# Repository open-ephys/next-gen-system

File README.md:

##  Next generation electrophysiology acquisition core
This repository is a work in progress repository for next generation open
source acquisition and closed-loop feedback system for multichannel
electrophysiology.

This project will hopefully end up being more than just an [open
ephys](http://www.open-ephys.org/) associated standard and will possibly be
moved to a different host org. Ideally we could end up with a set of open, and
evolving interface standards, code blocks and APIs that many different projects
can adapt parts of.

See the [working draft of the
specification](https://open-ephys.atlassian.net/wiki/display/OEW/PCIe+acquisition+board)
for details on the projects goals and desired features.

For now, we are aiming to build a working proof-of-principle prototype that we
can use as starting point to develop proper standards.

## License

### Hardware

<br/>
<span
    xmlns:dct="http://purl.org/dc/terms/" property="dct:title">Open Ephys FMC Intan IO module
</span> 
by 
<a xmlns:cc="http://creativecommons.org/ns#"
href="https://github.com/open-ephys/next-gen-system/" property="cc:attributionName"
rel="cc:attributionURL">Jonathan P. Newman, Jakob Voigts</a> 
is licensed under a
<a rel="license" href="http://creativecommons.org/licenses/by-sa/4.0/">Creative
Commons Attribution-ShareAlike 4.0 International
License</a>.
<br/>
Based on a work at <a xmlns:dct="http://purl.org/dc/terms/"
href="https://github.com/open-ephys/next-gen-system"
rel="dct:source">https://github.com/open-ephys/next-gen-system </a>

### Software
To be decided. Will likely be different licences for different layers of the
system (e.g. the firmware and devices drivers versus APIs and language bindings
versus plugins for various applications).

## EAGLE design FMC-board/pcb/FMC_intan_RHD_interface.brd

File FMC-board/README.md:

# FMC Daughter Board

### Documentation

This board roughly conforms to the VITA 57 standard for LPC (low pin count) FMCs (FPGA Mezzanine Card).

It contains:
- 3x direct SMA connectors to the fpga, with overvoltage diode protection.
- 2x intan compatible 12pin omnetics connectors (A & B) for the intan headstage SPI standard, wired directly to the fpga, with a power supply.
- 1x isolated intan compatible connector (C) isolated through LVDS to CMOS converters and galvanic isolators. This headstage has its own power supply that is fed through am isolated DC-DC converter.
- 3x directional SMA connectors (on the card front edge) that are routed through the same isolation circuit as headstage connector C

The overall proposed architecture of the system is outlined [here](https://open-ephys.atlassian.net/wiki/display/OEW/PCIe+acquisition+board)

### Pinout
FMC LPC pinout can be found [here](https://docs.google.com/spreadsheets/d/18WfmbLGt8bGUUdksKp6AKA_wMX2SJ3Tndin-nnEgUCs/edit#gid=584734392)

### BOM
The bill of materials for this device can be found
[here](https://docs.google.com/spreadsheets/d/18WfmbLGt8bGUUdksKp6AKA_wMX2SJ3Tndin-nnEgUCs/edit?usp=sharing).

## Manufacturing requirements
- 4 layers
- 8mil trace width & spacing
- 12mil min. drill

There is one 0.05" pitch BGA connector (the samtech FMC connector) and a few omnetics connectors with inacessible pins on the board, so a stencil and reflow soldering need to be used.

The samtech FMC connector might need to be clamped or held down during reflow soldering. The samtec docs state that they should settle on their own during reflow though, so trying that first seems like a good idea (  http://suddendocs.samtec.com/processing/searay_soldering1.pdf ).

There is a round pad of kapton tape on the connector to provide a clamping surface for this purpose. We have had good success with using a steel paperclip that we modified to exert less force by cutting two slots into the spring. The original paper clips push down too hard and can warp the conenctor. Possibly just weighting it down with a suitable object could also work. Finally, the size of the connector means that it heats up pretty slowly, so expect it to reflow after everything else on the board, and if possible use proper pre-heating.

In order to meet approximately correct trace impedances, the design further is assuming:
 - 1oz copper
 - ~1.2mm total board height, ~0.25mm per layer, dielectric ER = 4.5

## TODO (Rev 1.0)
- [ ] Instead of conforming to VITA 57, PCB footprint should be made to fit in
  a PC expansion slot and be connected to the KC705 using a flex [FMC
  cable](http://suddendocs.samtec.com/prints/hdr-169472-xx-mkt.pdf). This will
  modularize the IO modules, potentially creating an ecosystem of different
  modules for different applications. It will also use extremely standardized
  interface (rear PC expansion slots) which also have excellent
  electrical/mechanical characteristics.
    - A couple interesting IO Module ideas
        - Analog module (e.g. NI DAQ replacement with some beefy multiplex SAR
          ADC and DAC on it)
        - Isolated Intan module (Similar to existing design, featuring galvanic
          isolation)
        - Adjustable logic level digital IO module
        - SPI compression module
        - Etc...
- [ ] As per [page 24 of the KC705 user
  guide](http://www.xilinx.com/support/documentation/boards_and_kits/kc705/ug810_KC705_Eval_Bd.pdf)
  we need to jumper the TDI and TDO pins of our FMC connectors to allow pass
  through of JTAG signals so the FPGA can be programmed when the FMC module is
  connected.
- [ ] For galvanically isolated IO module, we should conform to human use
  standards. Jakob has some info on what is required for this.

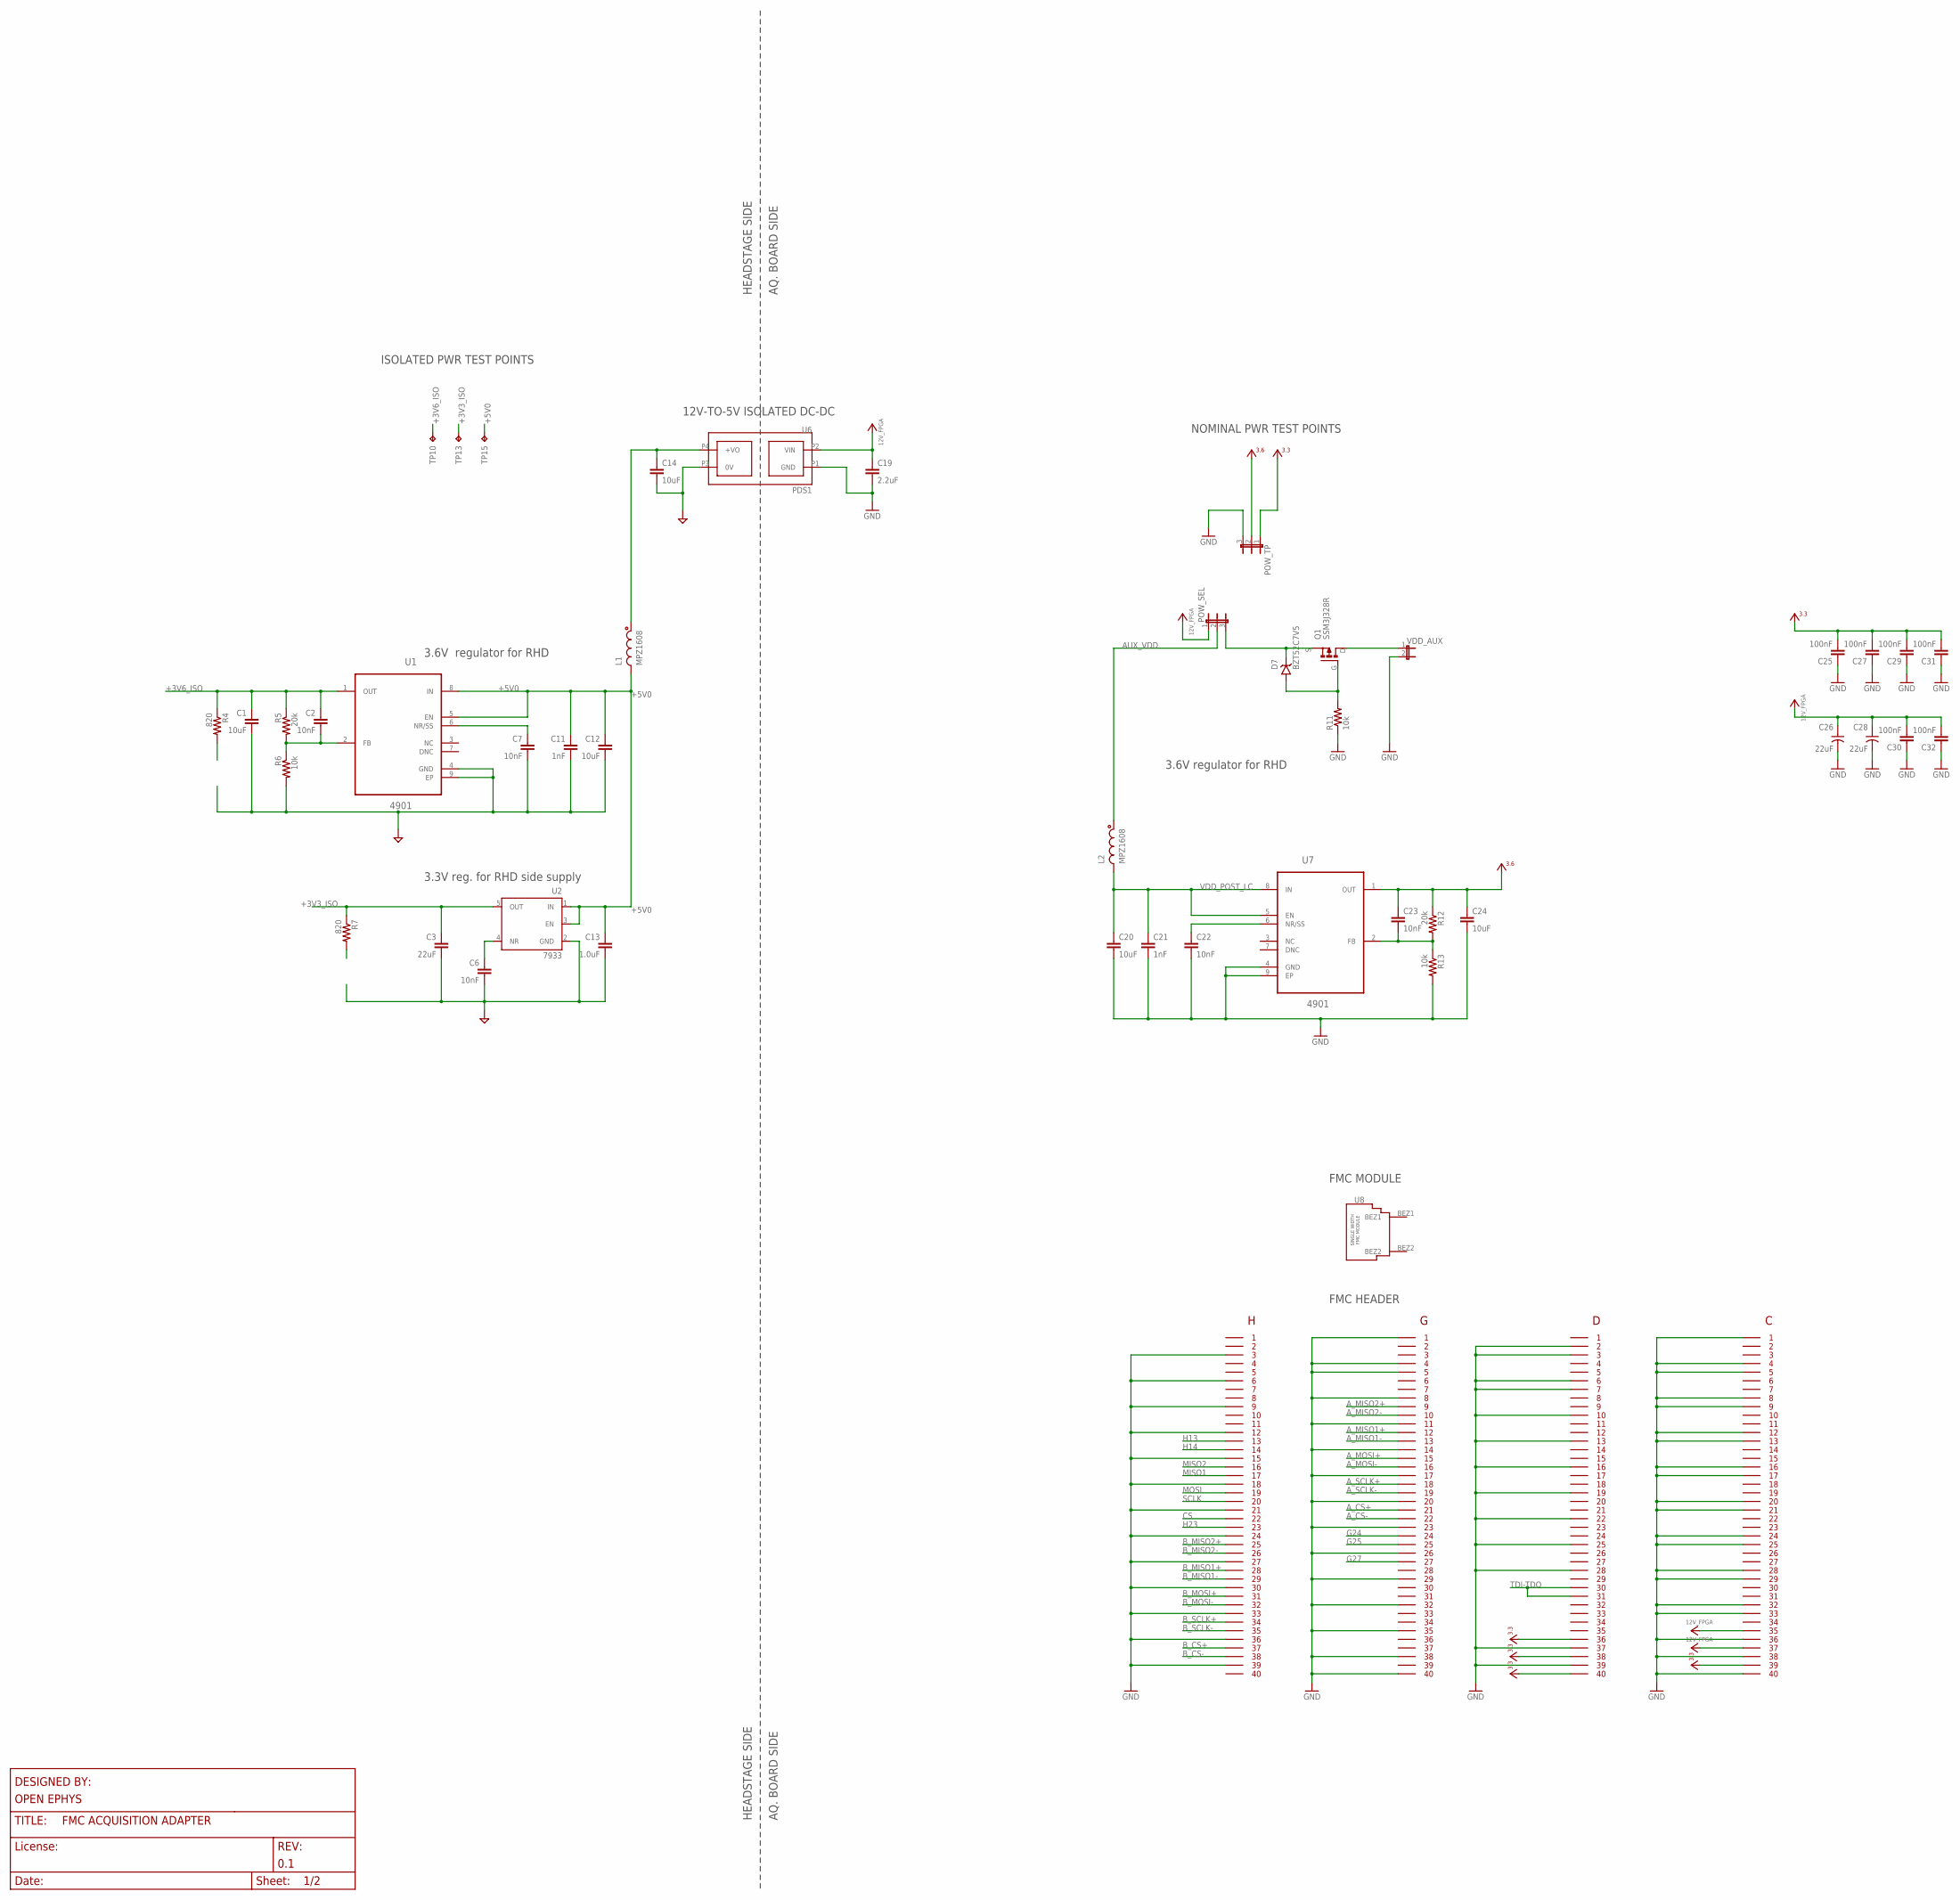
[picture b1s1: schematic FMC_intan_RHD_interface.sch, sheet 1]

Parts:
C1, C12, C14, C20, C24: 10uF; 1206
C2, C6, C7, C22, C23: 10nF; 0603
C3: 22uF; 1206
C11, C21: 1nF; 0603
C13: 1.0uF; 0805
C19: 2.2uF; 1206
C25, C27, C29, C30, C31, C32: 100nF; 0603
C26, C28: 22uF; 1210-POL
D7: BZT52C7V5; SOD123
FMC: FMC_LPC_160_PIN; FMC_LPC_MALE_WITH_SP601_BSILK
L1, L2: MPZ1608; 0603
POW_SEL: JP3E; JP3
POW_TP: JP3E; JP3
Q1: SSM3J328R; SOT23-GSD
R4, R7: 820; 0603
R5, R12: 20k; 0603
R6, R11, R13: 10k; 0603
TP10: +3V6; TP06R
TP13: +3V3; TP06R
TP15: +5V0; TP06R
U1, U7: 4901; SOP65P490X110-9N
U2: 7933; SOT-23-5
U6: PDS1
U8: FMC_SINGLE_WIDTH_MODULE
VDD_AUX: JP2E_THRU-HOLE; JP2

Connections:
12V_FPGA: C19.1, C26.+, C28.+, C30.2, C32.2, FMC.P$155, FMC.P$157, POW_SEL.1, U6.P2 (VIN)
+3V3: C25.2, C27.2, C29.2, C31.2, FMC.P$116, FMC.P$118, FMC.P$120, FMC.P$159, POW_TP.1; also elsewhere on the board
+3V3_ISO: C3.1, R7.1, TP13.TP, U2.5 (OUT); also elsewhere on the board
+3V6: C23.1, C24.1, POW_TP.2, R12.1, U7.1 (OUT)
+3V6_ISO: C1.1, C2.1, R4.1, R5.1, TP10.TP, U1.1 (OUT); also elsewhere on the board
+5V0: C11.1, C12.1, C13.1, L1.2, TP15.TP, U1.5 (EN), U1.8 (IN), U2.1 (IN), U2.3 (EN)
+5V0_ISO-PRE: C14.1, L1.1, U6.P4 (+VO)
AGND1: C23.2, R12.2, R13.1, U7.2 (FB)
AGND2: C2.2, R5.2, R6.1, U1.2 (FB)
AUX_VDD: L2.1, POW_SEL.2
A_CS+: FMC.P$61
A_CS-: FMC.P$62
A_MISO1+: FMC.P$52
A_MISO1-: FMC.P$53
A_MISO2+: FMC.P$49
A_MISO2-: FMC.P$50
A_MOSI+: FMC.P$55
A_MOSI-: FMC.P$56
A_SCLK+: FMC.P$58
A_SCLK-: FMC.P$59
B_CS+: FMC.P$37
B_CS-: FMC.P$38
B_MISO1+: FMC.P$28
B_MISO1-: FMC.P$29
B_MISO2+: FMC.P$25
B_MISO2-: FMC.P$26
B_MOSI+: FMC.P$31
B_MOSI-: FMC.P$32
B_SCLK+: FMC.P$34
B_SCLK-: FMC.P$35
CS: FMC.P$22; also elsewhere on the board
G24: FMC.P$64
G25: FMC.P$65
G27: FMC.P$67
GND: C19.2, C20.2, C21.2, C22.2, C24.2, C25.1, C26.-, C27.1, C28.-, C29.1, C30.1, C31.1, C32.1, FMC.GNDA (GND), FMC.GNDB (GND), FMC.P$3, FMC.P$6, FMC.P$9, FMC.P$12, FMC.P$15, FMC.P$18, FMC.P$21, FMC.P$24, FMC.P$27, FMC.P$30, FMC.P$33, FMC.P$36, FMC.P$39, FMC.P$41, FMC.P$44, FMC.P$45, FMC.P$48, FMC.P$51, FMC.P$54, FMC.P$57, FMC.P$60, FMC.P$63, FMC.P$66, FMC.P$69, FMC.P$72, FMC.P$75, FMC.P$78, FMC.P$80, FMC.P$82, FMC.P$83, FMC.P$86, FMC.P$87, FMC.P$90, FMC.P$93, FMC.P$96, FMC.P$99, FMC.P$102, FMC.P$105, FMC.P$108, FMC.P$117, FMC.P$119, FMC.P$121, FMC.P$124, FMC.P$125, FMC.P$128, FMC.P$129, FMC.P$132, FMC.P$133, FMC.P$136, FMC.P$137, FMC.P$140, FMC.P$141, FMC.P$144, FMC.P$145, FMC.P$148, FMC.P$149, FMC.P$152, FMC.P$153, FMC.P$156, FMC.P$158, FMC.P$160, POW_TP.3, R11.1, R13.2, U6.P1 (GND), U7.4 (GND), U7.9 (EP), VDD_AUX.2; also elsewhere on the board
GND_ISO: C1.2, C3.2, C6.2, C7.2, C11.2, C12.2, C13.2, C14.2, R6.2, U1.4 (GND), U1.9 (EP), U2.2 (GND), U6.P3 (0V); also elsewhere on the board
H13: FMC.P$13; also elsewhere on the board
H14: FMC.P$14; also elsewhere on the board
H23: FMC.P$23; also elsewhere on the board
MISO1: FMC.P$17; also elsewhere on the board
MISO2: FMC.P$16; also elsewhere on the board
MOSI: FMC.P$19; also elsewhere on the board
unnamed: C22.1, U7.6 (NR/SS)
unnamed: D7.C, POW_SEL.3, Q1.S
unnamed: C7.1, U1.6 (NR/SS)
unnamed: D7.A, Q1.G, R11.2
unnamed: Q1.D, VDD_AUX.1
unnamed: C6.1, U2.4 (NR)
SCLK: FMC.P$20; also elsewhere on the board
TDI-TDO: FMC.P$110, FMC.P$111
VDD_POST_LC: C20.1, C21.1, L2.2, U7.5 (EN), U7.8 (IN)

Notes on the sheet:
HEADSTAGE SIDE
AQ. BOARD SIDE
3.3V reg. for RHD side supply
3.6V regulator for RHD
12V-TO-5V ISOLATED DC-DC
ISOLATED PWR TEST POINTS
NOMINAL PWR TEST POINTS
3.6V regulator for RHD
FMC HEADER
FMC MODULE

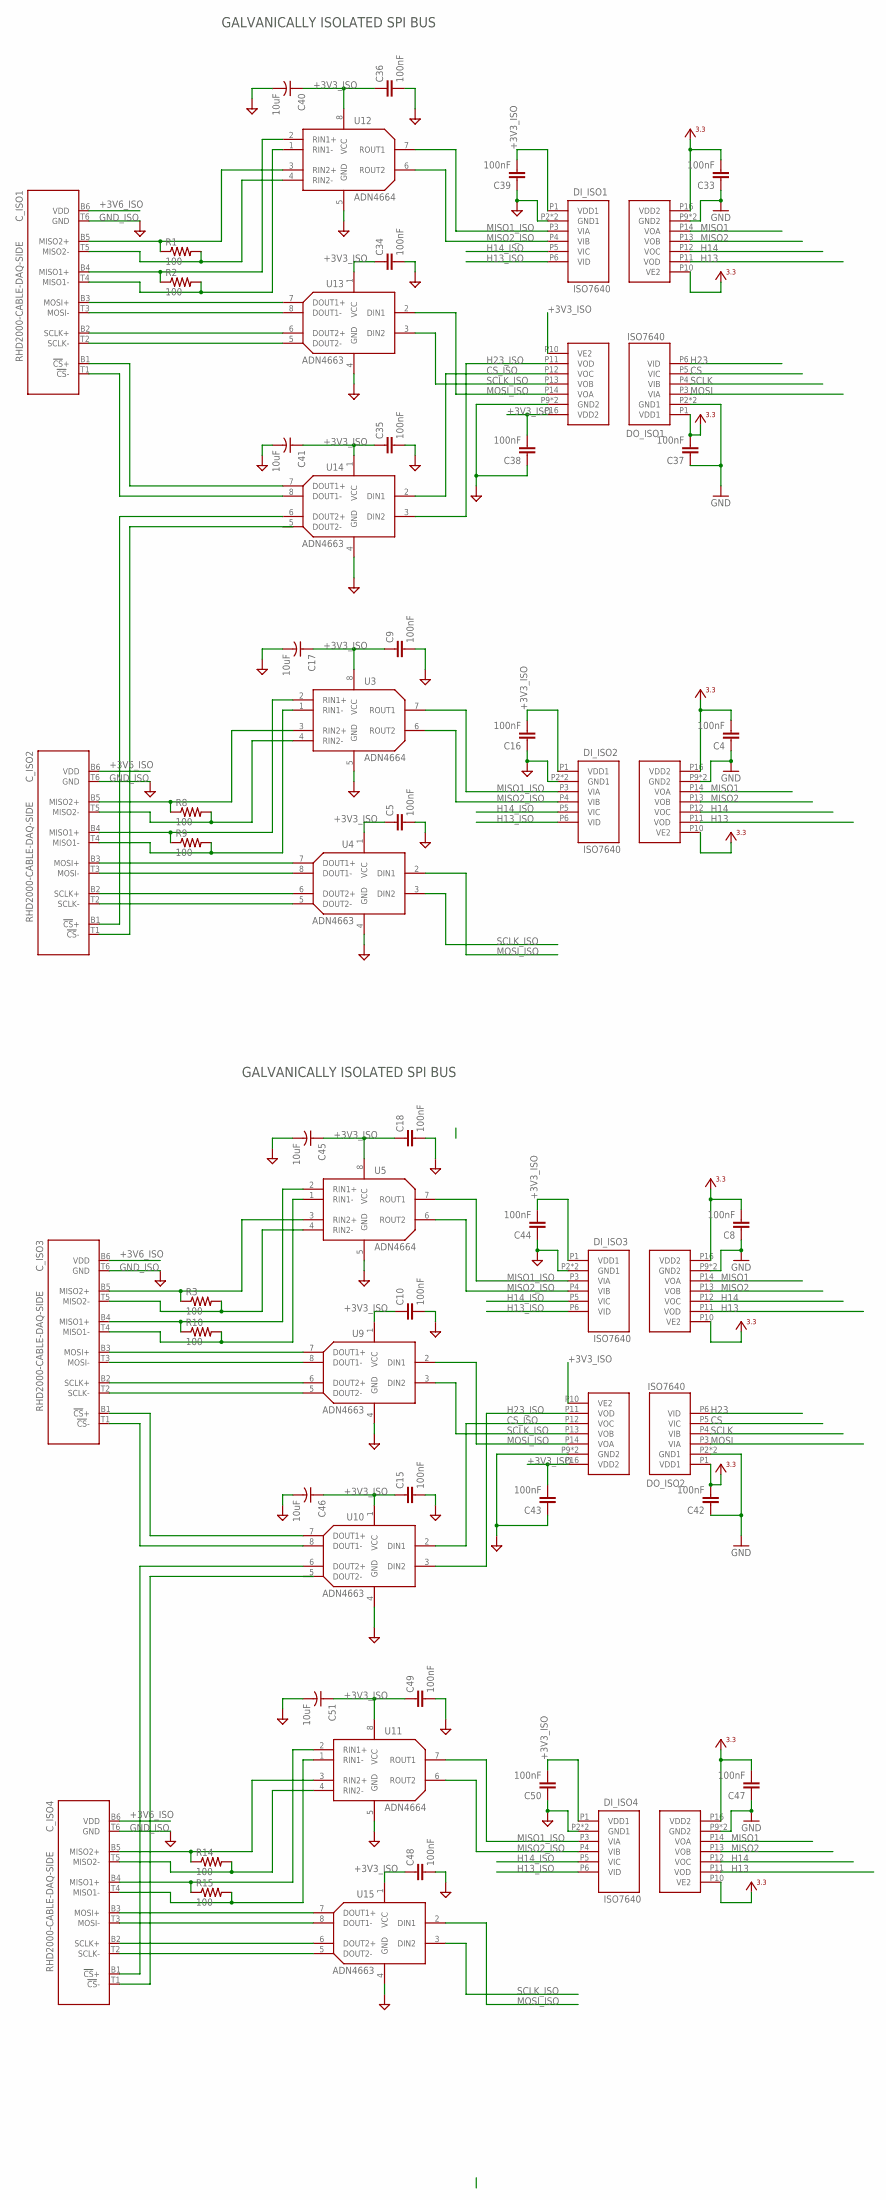
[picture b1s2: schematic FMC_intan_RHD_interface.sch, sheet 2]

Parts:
C4, C5, C8, C9, C10, C15, C16, C18, C33, C34, C35, C36, C37, C38, C39, C42, C43, C44, C47, C48, C49, C50: 100nF; 0603
C17, C40, C41, C45, C46, C51: 10uF; 1206-POL
C_ISO1, C_ISO2, C_ISO3, C_ISO4: RHD2000-CABLE-DAQ-SIDE; OMNETICS_PZN-12-AA
DI_ISO1, DI_ISO2, DI_ISO3, DI_ISO4: ISO7640; SOIC_WIDE_16
DO_ISO1, DO_ISO2: ISO7640; SOIC_WIDE_16
R1, R2, R3, R8, R9, R10, R14, R15: 100; 0603
U3, U5, U11, U12: ADN4664; SOIC127P500X400-8N
U4, U9, U10, U13, U14, U15: ADN4663; SOIC127P500X400-8N

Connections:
+3V3: C4.2, C8.2, C33.2, C37.2, C42.2, C47.2, DI_ISO1.P10 (VE2), DI_ISO1.P16 (VDD2), DI_ISO2.P10 (VE2), DI_ISO2.P16 (VDD2), DI_ISO3.P10 (VE2), DI_ISO3.P16 (VDD2), DI_ISO4.P10 (VE2), DI_ISO4.P16 (VDD2), DO_ISO1.P1 (VDD1), DO_ISO2.P1 (VDD1); also elsewhere on the board
+3V3_ISO: C5.1, C9.1, C10.1, C15.1, C16.2, C17.+, C18.1, C34.1, C35.1, C36.1, C38.2, C39.2, C40.+, C41.+, C43.2, C44.2, C45.+, C46.+, C48.1, C49.1, C50.2, C51.+, DI_ISO1.P1 (VDD1), DI_ISO2.P1 (VDD1), DI_ISO3.P1 (VDD1), DI_ISO4.P1 (VDD1), DO_ISO1.P10 (VE2), DO_ISO1.P16 (VDD2), DO_ISO2.P10 (VE2), DO_ISO2.P16 (VDD2), U3.8 (VCC), U4.1 (VCC), U5.8 (VCC), U9.1 (VCC), U10.1 (VCC), U11.8 (VCC), U12.8 (VCC), U13.1 (VCC), U14.1 (VCC), U15.1 (VCC); also elsewhere on the board
+3V6_ISO: C_ISO1.B6 (VDD), C_ISO2.B6 (VDD), C_ISO3.B6 (VDD), C_ISO4.B6 (VDD); also elsewhere on the board
CS: DO_ISO1.P5 (VIC), DO_ISO2.P5 (VIC); also elsewhere on the board
CS+_ISOLATED1: C_ISO1.B1 (!CS!+), U14.7 (DOUT1+)
CS+_ISOLATED2: C_ISO2.B1 (!CS!+)
CS+_ISOLATED3: C_ISO3.B1 (!CS!+), U10.7 (DOUT1+)
CS+_ISOLATED4: C_ISO4.B1 (!CS!+)
CS-_ISOLATED1: C_ISO1.T1 (!CS!-), U14.8 (DOUT1-)
CS-_ISOLATED2: C_ISO2.T1 (!CS!-)
CS-_ISOLATED3: C_ISO3.T1 (!CS!-), U10.8 (DOUT1-)
CS-_ISOLATED4: C_ISO4.T1 (!CS!-)
CS_ISO: DO_ISO1.P12 (VOC), DO_ISO2.P12 (VOC), U10.2 (DIN1), U14.2 (DIN1)
GND: C4.1, C8.1, C33.1, C37.1, C42.1, C47.1, DI_ISO1.P9 (GND2), DI_ISO1.P15 (GND2), DI_ISO2.P9 (GND2), DI_ISO2.P15 (GND2), DI_ISO3.P9 (GND2), DI_ISO3.P15 (GND2), DI_ISO4.P9 (GND2), DI_ISO4.P15 (GND2), DO_ISO1.P2 (GND1), DO_ISO1.P8 (GND1), DO_ISO2.P2 (GND1), DO_ISO2.P8 (GND1); also elsewhere on the board
GND_ISO: C5.2, C9.2, C10.2, C15.2, C16.1, C17.-, C18.2, C34.2, C35.2, C36.2, C38.1, C39.1, C40.-, C41.-, C43.1, C44.1, C45.-, C46.-, C48.2, C49.2, C50.1, C51.-, C_ISO1.T6 (GND), C_ISO2.T6 (GND), C_ISO3.T6 (GND), C_ISO4.T6 (GND), DI_ISO1.P2 (GND1), DI_ISO1.P8 (GND1), DI_ISO2.P2 (GND1), DI_ISO2.P8 (GND1), DI_ISO3.P2 (GND1), DI_ISO3.P8 (GND1), DI_ISO4.P2 (GND1), DI_ISO4.P8 (GND1), DO_ISO1.P9 (GND2), DO_ISO1.P15 (GND2), DO_ISO2.P9 (GND2), DO_ISO2.P15 (GND2), U3.5 (GND), U4.4 (GND), U5.5 (GND), U9.4 (GND), U10.4 (GND), U11.5 (GND), U12.5 (GND), U13.4 (GND), U14.4 (GND), U15.4 (GND); also elsewhere on the board
H13: DI_ISO1.P11 (VOD), DI_ISO2.P11 (VOD), DI_ISO3.P11 (VOD), DI_ISO4.P11 (VOD); also elsewhere on the board
H13_ISO: DI_ISO1.P6 (VID), DI_ISO2.P6 (VID), DI_ISO3.P6 (VID), DI_ISO4.P6 (VID)
H14: DI_ISO1.P12 (VOC), DI_ISO2.P12 (VOC), DI_ISO3.P12 (VOC), DI_ISO4.P12 (VOC); also elsewhere on the board
H14_ISO: DI_ISO1.P5 (VIC), DI_ISO2.P5 (VIC), DI_ISO3.P5 (VIC), DI_ISO4.P5 (VIC)
H23: DO_ISO1.P6 (VID), DO_ISO2.P6 (VID); also elsewhere on the board
H23_ISO: DO_ISO1.P11 (VOD), DO_ISO2.P11 (VOD), U10.3 (DIN2), U14.3 (DIN2)
MISO1: DI_ISO1.P14 (VOA), DI_ISO2.P14 (VOA), DI_ISO3.P14 (VOA), DI_ISO4.P14 (VOA); also elsewhere on the board
MISO1+_ISOLATED1: C_ISO1.B4 (MISO1+), R2.1, U12.2 (RIN1+)
MISO1+_ISOLATED2: C_ISO2.B4 (MISO1+), R9.1, U3.2 (RIN1+)
MISO1+_ISOLATED3: C_ISO3.B4 (MISO1+), R10.1, U5.2 (RIN1+)
MISO1+_ISOLATED4: C_ISO4.B4 (MISO1+), R15.1, U11.2 (RIN1+)
MISO1-_ISOLATED1: C_ISO1.T4 (MISO1-), R2.2, U12.1 (RIN1-)
MISO1-_ISOLATED2: C_ISO2.T4 (MISO1-), R9.2, U3.1 (RIN1-)
MISO1-_ISOLATED3: C_ISO3.T4 (MISO1-), R10.2, U5.1 (RIN1-)
MISO1-_ISOLATED4: C_ISO4.T4 (MISO1-), R15.2, U11.1 (RIN1-)
MISO1_ISO: DI_ISO1.P3 (VIA), DI_ISO2.P3 (VIA), DI_ISO3.P3 (VIA), DI_ISO4.P3 (VIA), U3.7 (ROUT1), U5.7 (ROUT1), U11.7 (ROUT1), U12.7 (ROUT1)
MISO2: DI_ISO1.P13 (VOB), DI_ISO2.P13 (VOB), DI_ISO3.P13 (VOB), DI_ISO4.P13 (VOB); also elsewhere on the board
MISO2+_ISOLATED1: C_ISO1.B5 (MISO2+), R1.1, U12.3 (RIN2+)
MISO2+_ISOLATED2: C_ISO2.B5 (MISO2+), R8.1, U3.3 (RIN2+)
MISO2+_ISOLATED3: C_ISO3.B5 (MISO2+), R3.1, U5.3 (RIN2+)
MISO2+_ISOLATED4: C_ISO4.B5 (MISO2+), R14.1, U11.3 (RIN2+)
MISO2-_ISOLATED1: C_ISO1.T5 (MISO2-), R1.2, U12.4 (RIN2-)
MISO2-_ISOLATED2: C_ISO2.T5 (MISO2-), R8.2, U3.4 (RIN2-)
MISO2-_ISOLATED3: C_ISO3.T5 (MISO2-), R3.2, U5.4 (RIN2-)
MISO2-_ISOLATED4: C_ISO4.T5 (MISO2-), R14.2, U11.4 (RIN2-)
MISO2_ISO: DI_ISO1.P4 (VIB), DI_ISO2.P4 (VIB), DI_ISO3.P4 (VIB), DI_ISO4.P4 (VIB), U3.6 (ROUT2), U5.6 (ROUT2), U11.6 (ROUT2), U12.6 (ROUT2)
MOSI: DO_ISO1.P3 (VIA), DO_ISO2.P3 (VIA); also elsewhere on the board
MOSI_ISO: DO_ISO1.P14 (VOA), DO_ISO2.P14 (VOA), U4.2 (DIN1), U9.2 (DIN1), U13.2 (DIN1), U15.2 (DIN1)
unnamed: C_ISO3.B3 (MOSI+), U9.7 (DOUT1+)
unnamed: C_ISO1.B3 (MOSI+), U13.7 (DOUT1+)
unnamed: C_ISO1.T3 (MOSI-), U13.8 (DOUT1-)
unnamed: C_ISO2.B3 (MOSI+), U4.7 (DOUT1+)
unnamed: C_ISO2.T3 (MOSI-), U4.8 (DOUT1-)
unnamed: C_ISO1.B2 (SCLK+), U13.6 (DOUT2+)
unnamed: C_ISO2.B2 (SCLK+), U4.6 (DOUT2+)
unnamed: C_ISO2.T2 (SCLK-), U4.5 (DOUT2-)
unnamed: C_ISO1.T2 (SCLK-), U13.5 (DOUT2-)
unnamed: C_ISO3.T3 (MOSI-), U9.8 (DOUT1-)
unnamed: C_ISO3.B2 (SCLK+), U9.6 (DOUT2+)
unnamed: C_ISO3.T2 (SCLK-), U9.5 (DOUT2-)
unnamed: C_ISO4.B3 (MOSI+), U15.7 (DOUT1+)
unnamed: C_ISO4.T3 (MOSI-), U15.8 (DOUT1-)
unnamed: C_ISO4.B2 (SCLK+), U15.6 (DOUT2+)
unnamed: C_ISO4.T2 (SCLK-), U15.5 (DOUT2-)
SCLK: DO_ISO1.P4 (VIB), DO_ISO2.P4 (VIB); also elsewhere on the board
SCLK_ISO: DO_ISO1.P13 (VOB), DO_ISO2.P13 (VOB), U4.3 (DIN2), U9.3 (DIN2), U13.3 (DIN2), U15.3 (DIN2)

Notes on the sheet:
GALVANICALLY ISOLATED SPI BUS

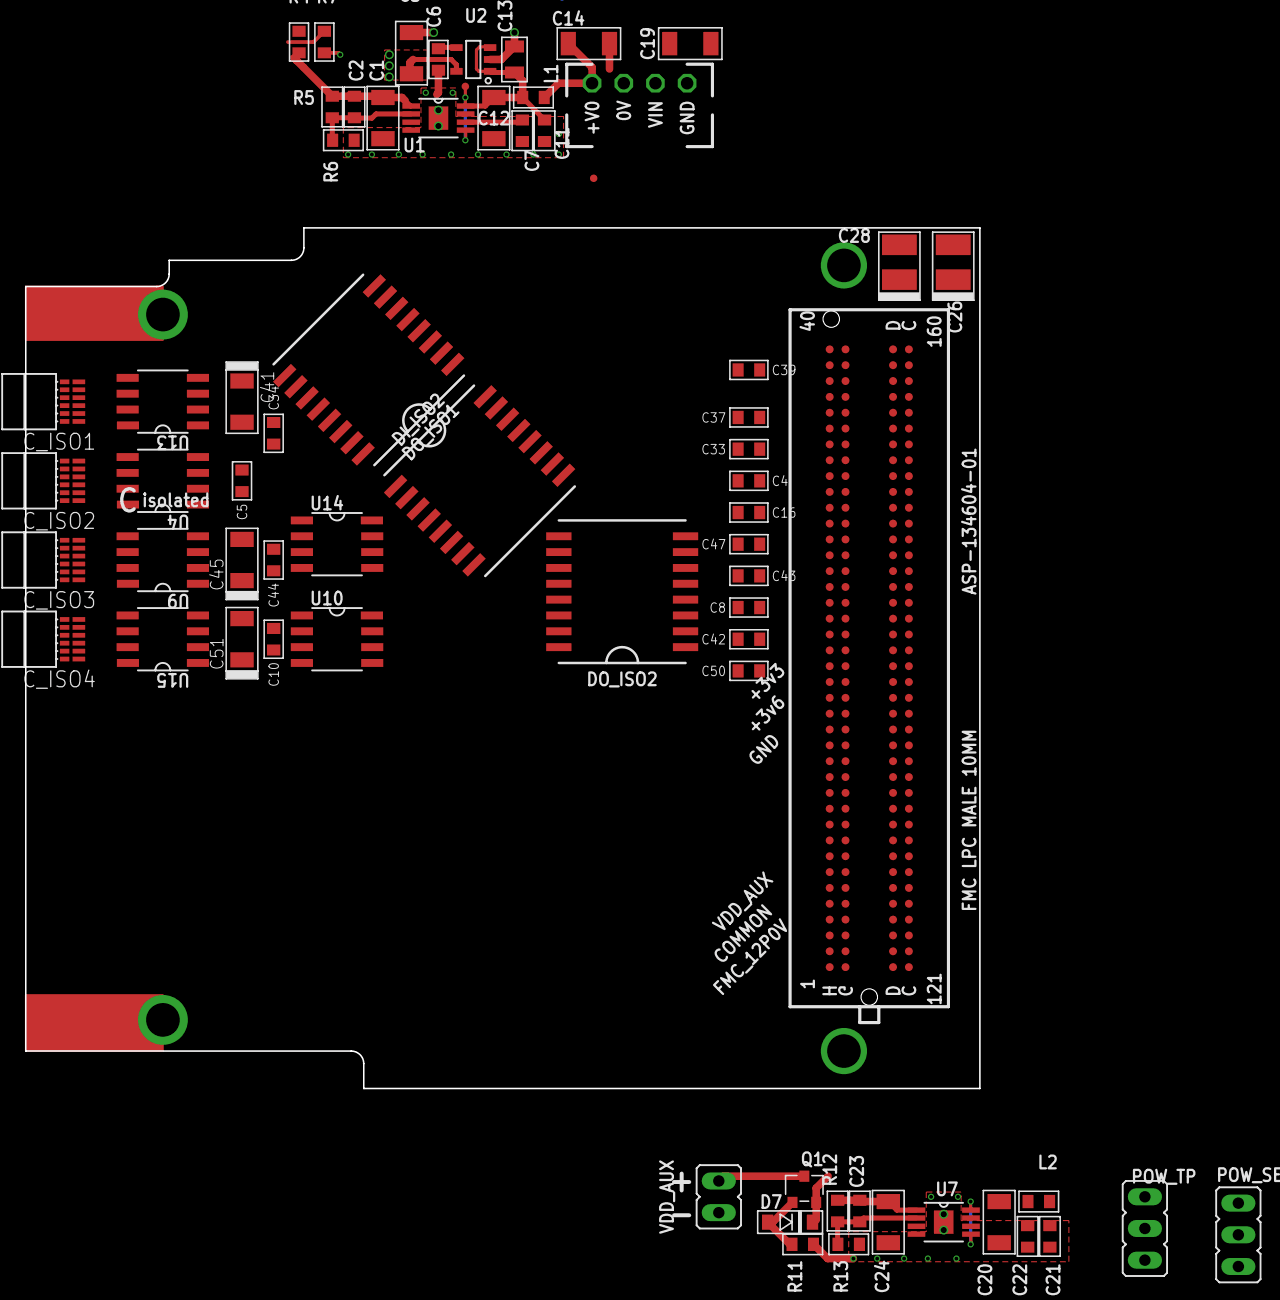
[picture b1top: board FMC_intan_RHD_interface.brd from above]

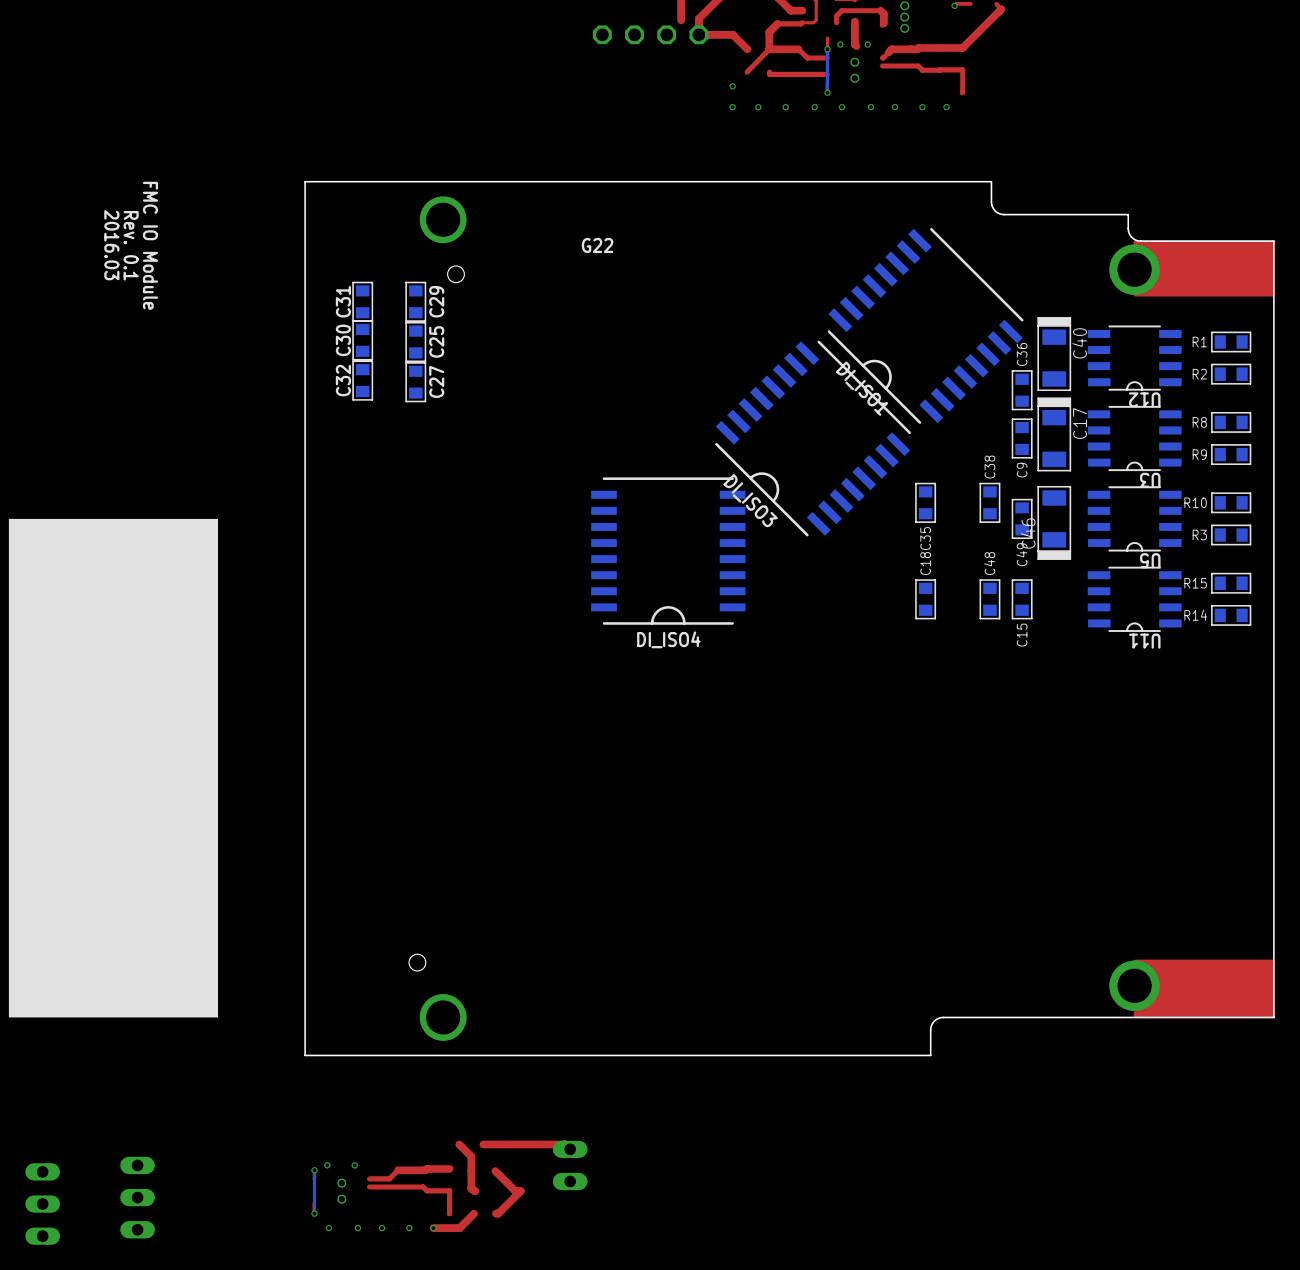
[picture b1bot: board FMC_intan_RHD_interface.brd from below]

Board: 4 copper layers, 76.5 x 69.0 mm, 102 parts (33 on the bottom side), 72 nets.

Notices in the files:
README.md:
alt="Creative Commons License" style="border-width:0"
src="https://i.creativecommons.org/l/by-sa/4.0/88x31.png" />
